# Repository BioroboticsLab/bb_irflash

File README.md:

# bb_irflash - Infrared LED flashing software and hardware

----
## What is bb_irflash?

bb_irflash is a software and hardware layout package. It contains the circuit and board layout for creating infrared flashing devices.

## Software

The software is C code written and tested for the Arduino Board Duemilanove. However, it should be easily adjusted to fit any arduino available on the market.

## Hardware

The hardware is designed to be triggered via signal current and powered with 12V. The design contains no protection mechanism whatsoever. So exchanging the resistors and/or LED's enables faster/slower flashing or constant lighting. 

The board dimensions are 23mmx51mm, single sided layout. Parts as described in the 'Parts' section enable flashing at 3 Hz and 20 ms duration. Designs come in EAGLE format.

# Parts

## SMD Parts Required for the Boards

The following Surface-Mount Device (SMD) parts are required for the boards:

### MOSFETs
- 8x [NTMS4807NR2G 'AO4752'](https://www.mouser.de/ProductDetail/863-NTMS4807NR2G)

### LEDs
- 8x [LED OSRAM 'SFH 4716AS A01'](https://www.mouser.de/ProductDetail/ams-OSRAM/SFH-4716AS-A01?qs=%252BEew9%252B0nqrDXvNyoSKrong%3D%3D)

### Signal Amplifiers
- 4x [Signal Amplifier 'LM358LVIDR'](https://www.mouser.de/ProductDetail/595-LM358LVIDR)

### Resistors
- 32x [2 Ohm Resistor '603-RC2512JK-072RL'](https://www.mouser.de/ProductDetail/603-RC2512JK-072RL)
- 16x [10k Ohm Resistor '71-CRCW060310K0JNEAC'](https://www.mouser.de/ProductDetail/71-CRCW060310K0JNEAC)
- 2x [4.7k Ohm Resistor '71-CRCW06034K70JNEAC'](https://www.mouser.de/ProductDetail/71-CRCW06034K70JNEAC)
- 4x [22k Ohm Resistor '71-CRCW060322K0JNEAC'](https://www.mouser.de/ProductDetail/71-CRCW060322K0JNEAC)
- 1x [20k Ohm Resistor 'R0603'](Beta Layout standard part) [20k Resistor on Mouser '71-CRCW060320K0JNEA'](https://www.mouser.de/ProductDetail/71-CRCW060320K0JNEAC)
)
- 1x [100k Ohm Resistor '71-CRCW0603100KFKEAC'](https://www.mouser.de/ProductDetail/71-CRCW0603100KFKEAC)

### Capacitors
- 4x [0.01uF Capacitor '810-C1005X7R1H103KBE'](https://www.mouser.de/ProductDetail/810-C1005X7R1H103KBE)
- 2x [1uF Capacitor '81-GRM155R61C105MA2D'](https://www.mouser.de/ProductDetail/81-GRM155R61C105MA2D)

### Diodes
- 2x [Schottky Diode 'CDBU0230R-HF'](https://www.mouser.de/ProductDetail/750-CDBU0230R-HF)

### Transistors
- 2x [NPN Transistor 'NSVMMBT2222AM3T5G'](https://www.mouser.de/ProductDetail/863-NSVMMBT2222AM3T5)

### Timer
- 2x [Timer 'NE555DR'](https://www.mouser.de/ProductDetail/595-NE555DR)

### Logic Gates
- 1x [Dual AND Gate '74LVC2G08'](https://www.mouser.de/ProductDetail/771-74LVC2G08DP-G)

## Through-hole-technology (THT) required components to solder on

### Capacitors
- 8x [2mF Capacitor '667-EEU-FP1E202B'](https://www.mouser.de/ProductDetail/667-EEU-FP1E202B)

### MOSFET
- 1x [STD12NF06L-1 'STD12NF06L-1'](https://www.mouser.de/ProductDetail/511-STD12NF06L-1)

### Connectors
- 8x [Header - Board to LED connections](https://www.mouser.de/ProductDetail/538-43045-0400)
- 1x [Header - Arduino connection](https://www.mouser.de/ProductDetail/538-105313-1203).  Note that the picture shows the incorrect part with number 1103.  The right angle connection
- 1x [Header - Power supply connection](https://www.mouser.de/ProductDetail/538-76825-0002)

See order_examples for further detail, and reference the picture for needed parts.  

# Mouser project order templates for parts:
- [bb_irflash SMD components Mouser project to order](https://eu.mouser.com/ProjectManager/ProjectDetail.aspx?AccessID=517e59b65d)
- [bb_irflash SMD components spreadsheet list](order_examples/BB_IRFLASH_SMD_COMPONENTS.xls)
- [bb_irflash THT components Mouser project to order](https://eu.mouser.com/ProjectManager/ProjectDetail.aspx?AccessID=0B309C354D)
- [bb_irflash THT components spreadsheet list](order_examples/BB_IRFLASH_THT_COMPONENTS.xls)
- [Cables for connecting lights, Arduino, and power supply](https://www.mouser.de/ProjectManager/ProjectDetail.aspx?AccessID=e691302b18). Note that the Arduino connection cable (Nanofit) and the power supply cable (Megafit) connect to the board, but will have to be cut/adjusted to make appropriate connections to the Arduino/power supply

# Power supply
The board is typically driven at 5V.  However, higher light output can be achieved by driving at slightly higher voltages.  here are suitable power supply for these voltages.  Note that when operating at 6fps and 5msec flashes, one board will draw 1-1.5 amps maximum.  Therefore one of these power supplies is sufficient to drive multiple boards.
- [5V power supply (adjustable in range 4.75-5.8V)](https://www.mouser.de/ProductDetail/MEAN-WELL/HRP-100-5?qs=Pc4kzEvJlcQLHIPhYtoJzw%3D%3D)
- [7.5V power supply (adjustable in range 6-9V)](https://www.mouser.de/ProductDetail/MEAN-WELL/RSP-320-7.5?qs=Uzd%2Fwh%252BZzhAvdwoq1II01Q%3D%3D).  Also available at [Conrad](https://www.conrad.de/de/p/mean-well-rsp-320-7-5-schaltnetzteil-7-5-v-dc-40-a-300-w-2249344.html?utm_source=google&utm_medium=cpc&utm_campaign=GB1_Messtechnik+%26+Stromversorgung_Generic&utm_id=43483581&gad_source=1&gbraid=0AAAAAD1-3H5RXiWIoMa0wxSd_K8oRlJKH&gclid=CjwKCAiAudG5BhAREiwAWMlSjDPmVMJK24BTLvHd9yjfUtIwc8q5r0EybappmSUyCZYAYHu7tNM5choC1wwQAvD_BwE&refresh=true)

# Board V2.0

The new IR flash board have the exact same performance as the previous version. The only new part is a better connectivity and a protection circuit.
The protection circuit is limiting the impulse duration to 20ms with a pause of 100ms between each pulse for protecting the LED. The power supply should be 
V ; 6A. To use it just send a step signal of the wanted duration to the trigger pin of the board (The step signal should not be wider than 20ms high and a pause of 100ms should be observe between each pulse)

The files in "board_V2" folder are all the project file in KiCAD format. If you have no interest in redesign, they are not interesting for you. 

For fabrication you only need the files in the fabrication folder.
The gerber files contained in "fabrication/gerber" are the map of your circuits - You manufacturer would ask for them (likely as a zip file, i.e. gerber.zip containing all folder contents).  The subfolder : "fabrication/gerber/drill_file" contain the coordinate of all the holes drilled into the board.

If you want to ask a third party for assembly, you will need the gerber files, the components position files ("Bestückungsplan": assembly_map_top.pdf
and assembly_map_bottom.pdf), the Pick&Place placement file (Pick&Place.txt), and the components list (Bill of Materials: BOM.xlsx). The 
The components position files are in component_position folder (Bottom and top layer). Note that the BOM format can vary in function of your third party company.

The folder order_examples contains two examples for orders placed through Beta Layout with components ordered through Mouser.  These are for reference.

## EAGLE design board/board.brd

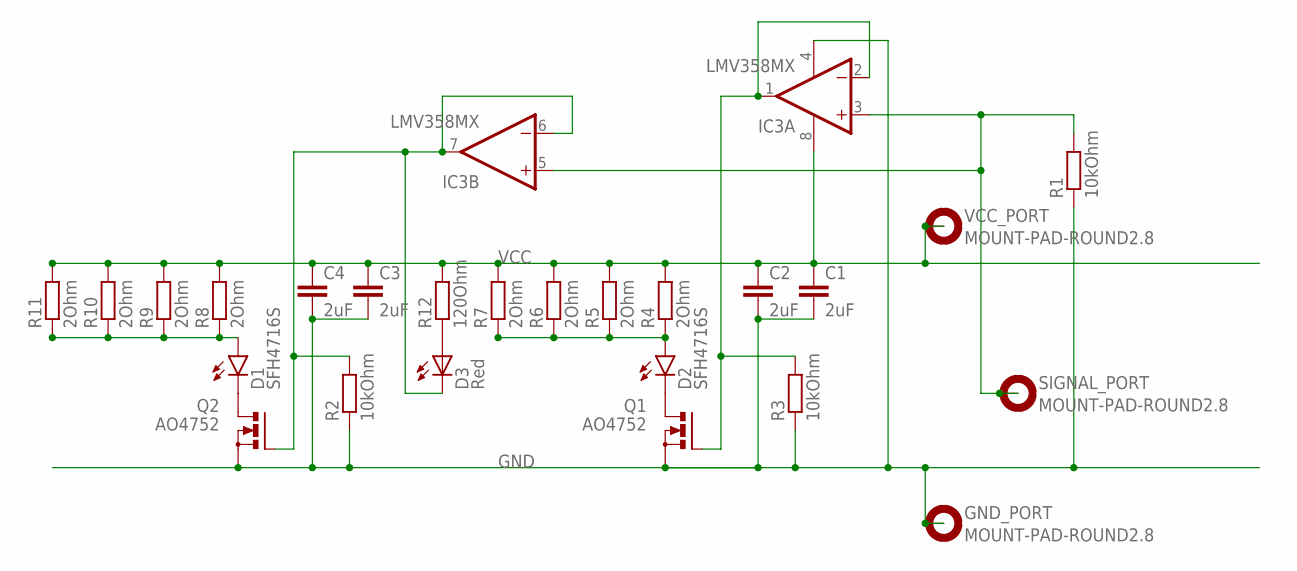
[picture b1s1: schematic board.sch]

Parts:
C1, C2, C3, C4: 2uF; C0603
D1, D2: SFH4716S; SFH4641
D3: Red; LED5MM
GND_PORT: MOUNT-PAD-ROUND2.8; 2,8-PAD
IC3: LMV358MX; SO08
Q1, Q2: AO4752; SO-08
R1, R2, R3: 10kOhm; R0603
R4, R5, R6, R7, R8, R9, R10, R11: 2Ohm; R2512
R12: 120Ohm; R0603
SIGNAL_PORT: MOUNT-PAD-ROUND2.8; 2,8-PAD
VCC_PORT: MOUNT-PAD-ROUND2.8; 2,8-PAD

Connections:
F1: D2.C, Q1.5 (D), Q1.6 (D), Q1.7 (D), Q1.8 (D)
F2: D1.C, Q2.5 (D), Q2.6 (D), Q2.7 (D), Q2.8 (D)
GND: C1.2, C2.2, C3.2, C4.2, GND_PORT.B2,8, IC3.4 (V-), Q1.1 (S), Q1.2 (S), Q1.3 (S), Q2.1 (S), Q2.2 (S), Q2.3 (S), R1.1, R2.1, R3.1
L1: D1.A, R8.1, R9.1, R10.1, R11.1
L2: D2.A, R4.1, R5.1, R6.1, R7.1
unnamed: D3.A, R12.1
unnamed: D3.K (C), IC3.6 (-IN), IC3.7 (OUT), Q2.4 (G), R2.2
unnamed: IC3.3 (+IN), IC3.5 (+IN), R1.2, SIGNAL_PORT.B2,8
unnamed: IC3.1 (OUT), IC3.2 (-IN), Q1.4 (G), R3.2
VCC: C1.1, C2.1, C3.1, C4.1, IC3.8 (V+), R4.2, R5.2, R6.2, R7.2, R8.2, R9.2, R10.2, R11.2, R12.2, VCC_PORT.B2,8

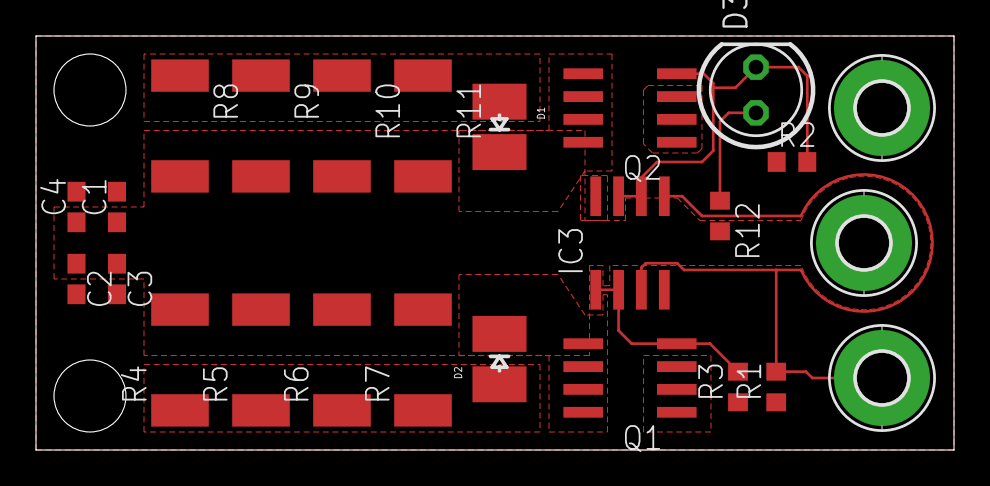
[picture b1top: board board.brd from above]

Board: 1 copper layer, 51.0 x 23.0 mm, 25 parts (0 on the bottom side), 10 nets.

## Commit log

2019-07-24 added original files scavenged from some old PC
2019-07-24 added coded modified on 2018 with more accurate delays and less jitter
2019-07-24 increased time between frames a little
2020-02-12 added simultaneous trigger added folder structure for different firmware variants
2020-02-14 Adding V2 board
2020-02-18 fixed bug in ms / us waiting time calculation
2020-02-18 completing README
2024-03-20 updated part numbers, cleaned up contents, added order examples
    Note: removed 'HiveCam' folder, because its contents were the same as board_v2. Moved PDFs with order details to separate folder, updated component links to Mouser, and included updated bill of mater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
2024-08-29 Create LICENSE
2024-11-12 added xls Mouser component lists
2025-02-06 update variable name
2025-02-20 Add 3D enclosure model files
2026-04-16 mosfet corrected to tht version
2026-04-16 add order including THT components
2026-04-22 replace mosfet due to end-of-life for other part

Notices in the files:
parts and their libraries:
SparkFun-LED: Licensing: Creative Commons ShareAlike 4.0 International - https://creativecommons.org/licenses/by-sa/4.0
